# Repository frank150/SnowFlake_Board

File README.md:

# SnowFlake_Board
Circuito impreso navideño en forma de copo de nieve.
# Descripción
Esta PCB es un copo de nieve para decorar tu arbolito navideño el cual encenderá led multicolor de destello lento
# Lista de componentes
Lista de componentes electrónicos usados:
* 6 RGB0807
* 1 Batt HLD-001
* 1 Switch 1825232-1

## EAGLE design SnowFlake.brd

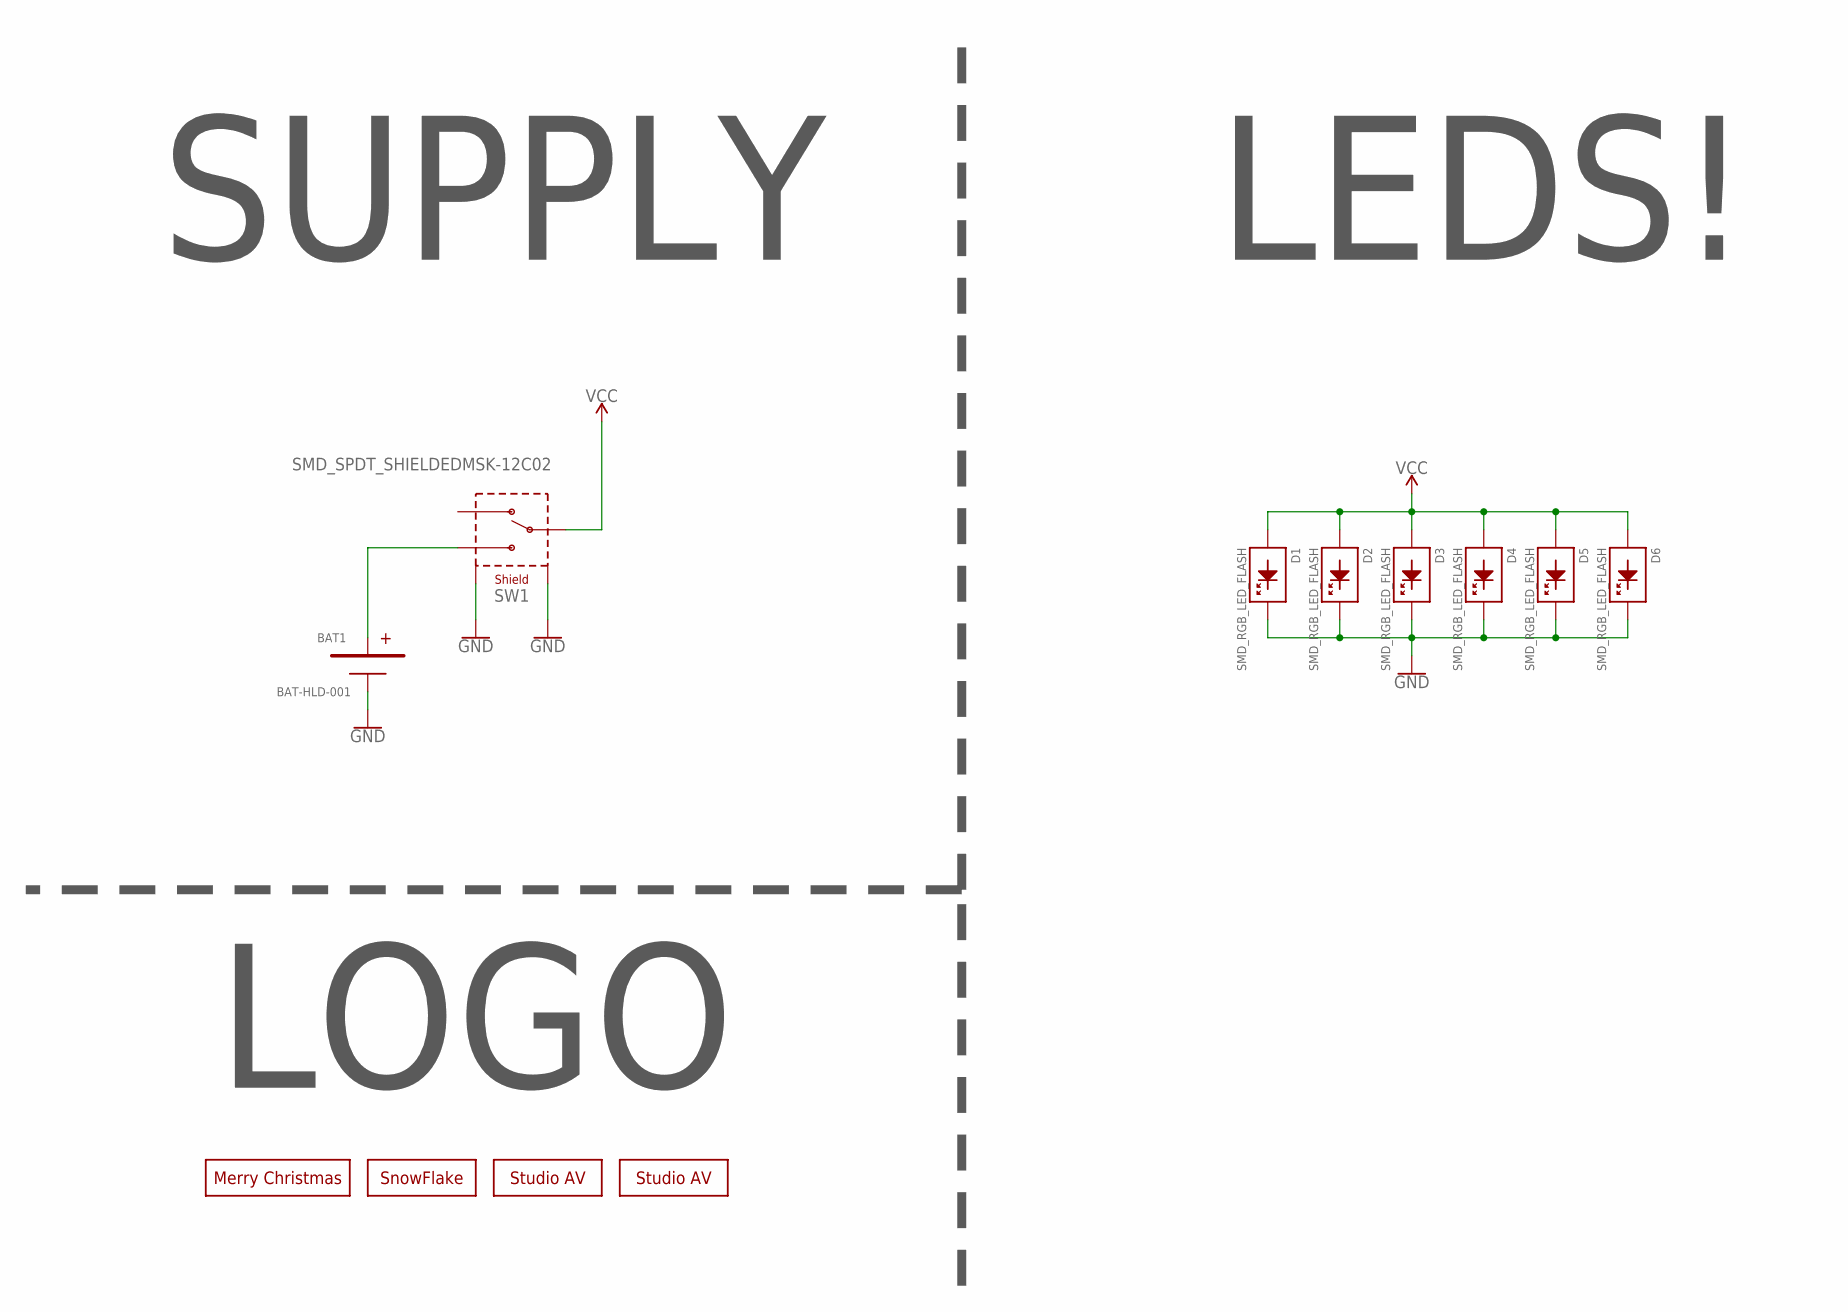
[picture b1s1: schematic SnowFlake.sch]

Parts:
BAT1: BAT-HLD-001; BATHLD001
D1, D2, D3, D4, D5, D6: SMD_RGB_LED_FLASH; SMD_RGB_LED_0807
SW1: SMD_SPDT_SHIELDEDMSK-12C02; MSK-12C02
U$1: MERRY_CHRISTMAS
U$2: STUDIO_AV-QR_CODE; STUDIO_AV_QR
U$3: STUDIO_AV-GENERAL; STUDIO_AV
U$4: SNOWFLAKE

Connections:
GND: BAT1.3 (N), D1.3 (K), D1.4 (K), D2.3 (K), D2.4 (K), D3.3 (K), D3.4 (K), D4.3 (K), D4.4 (K), D5.3 (K), D5.4 (K), D6.3 (K), D6.4 (K), SW1.GND@1 (S1), SW1.GND@2 (S2), SW1.GND@3 (S1), SW1.GND@4 (S2)
unnamed: BAT1.1, BAT1.2, SW1.L2 (NO)
VCC: D1.1 (A), D1.2 (A), D2.1 (A), D2.2 (A), D3.1 (A), D3.2 (A), D4.1 (A), D4.2 (A), D5.1 (A), D5.2 (A), D6.1 (A), D6.2 (A), SW1.COM (C)

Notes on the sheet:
SUPPLY
LEDS!
LOGO

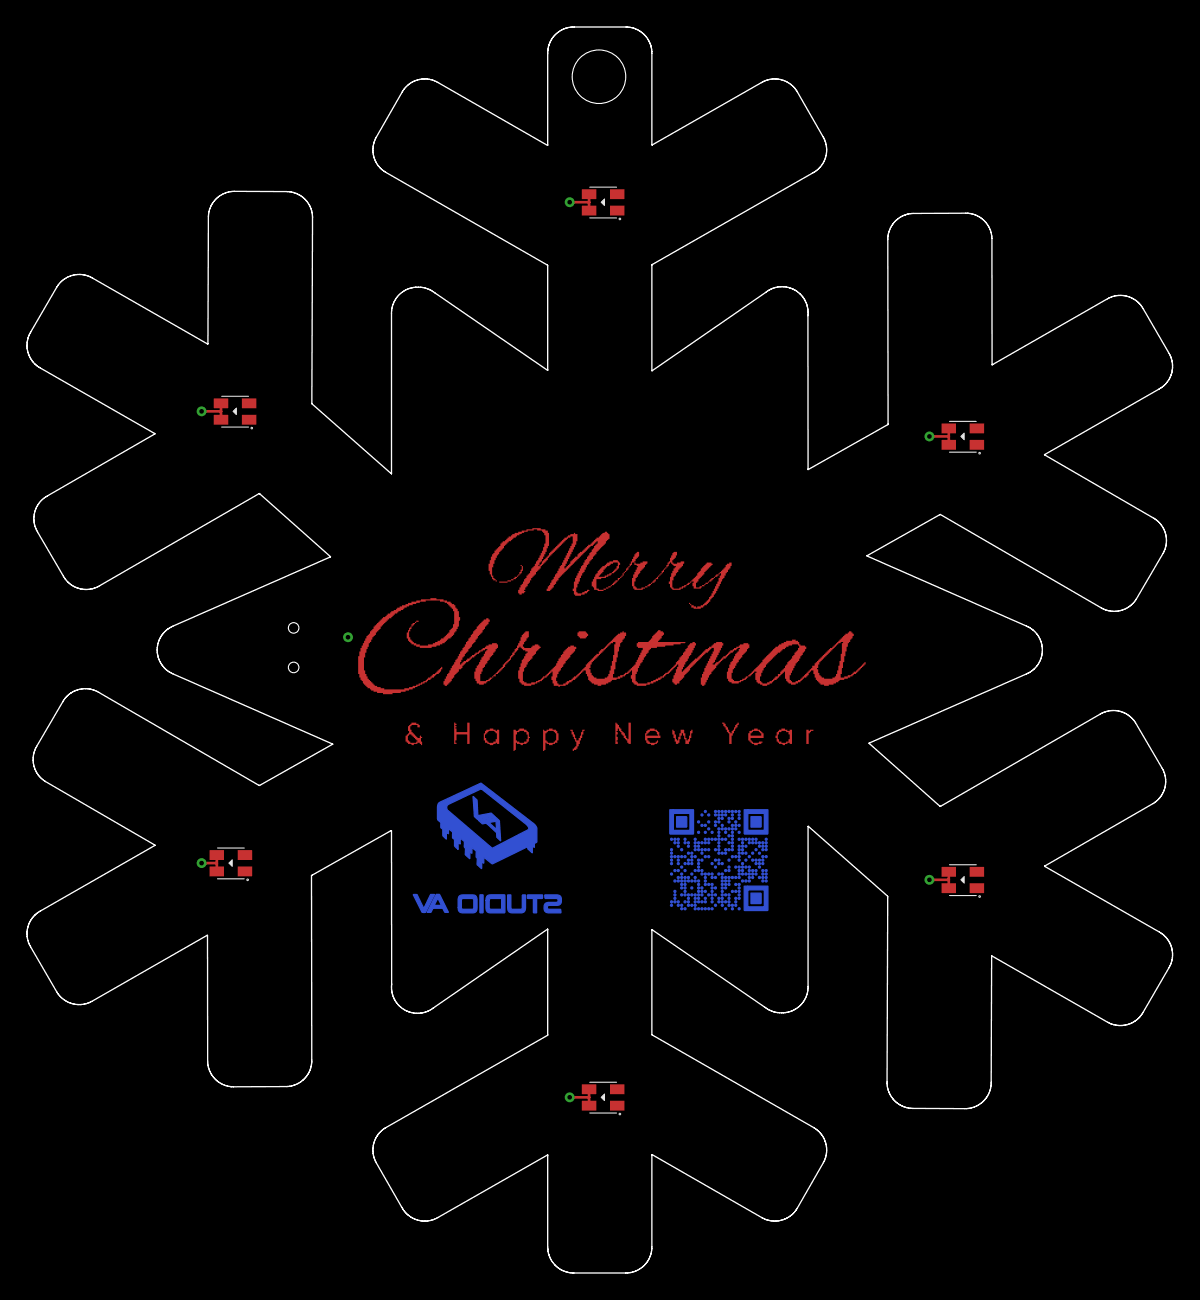
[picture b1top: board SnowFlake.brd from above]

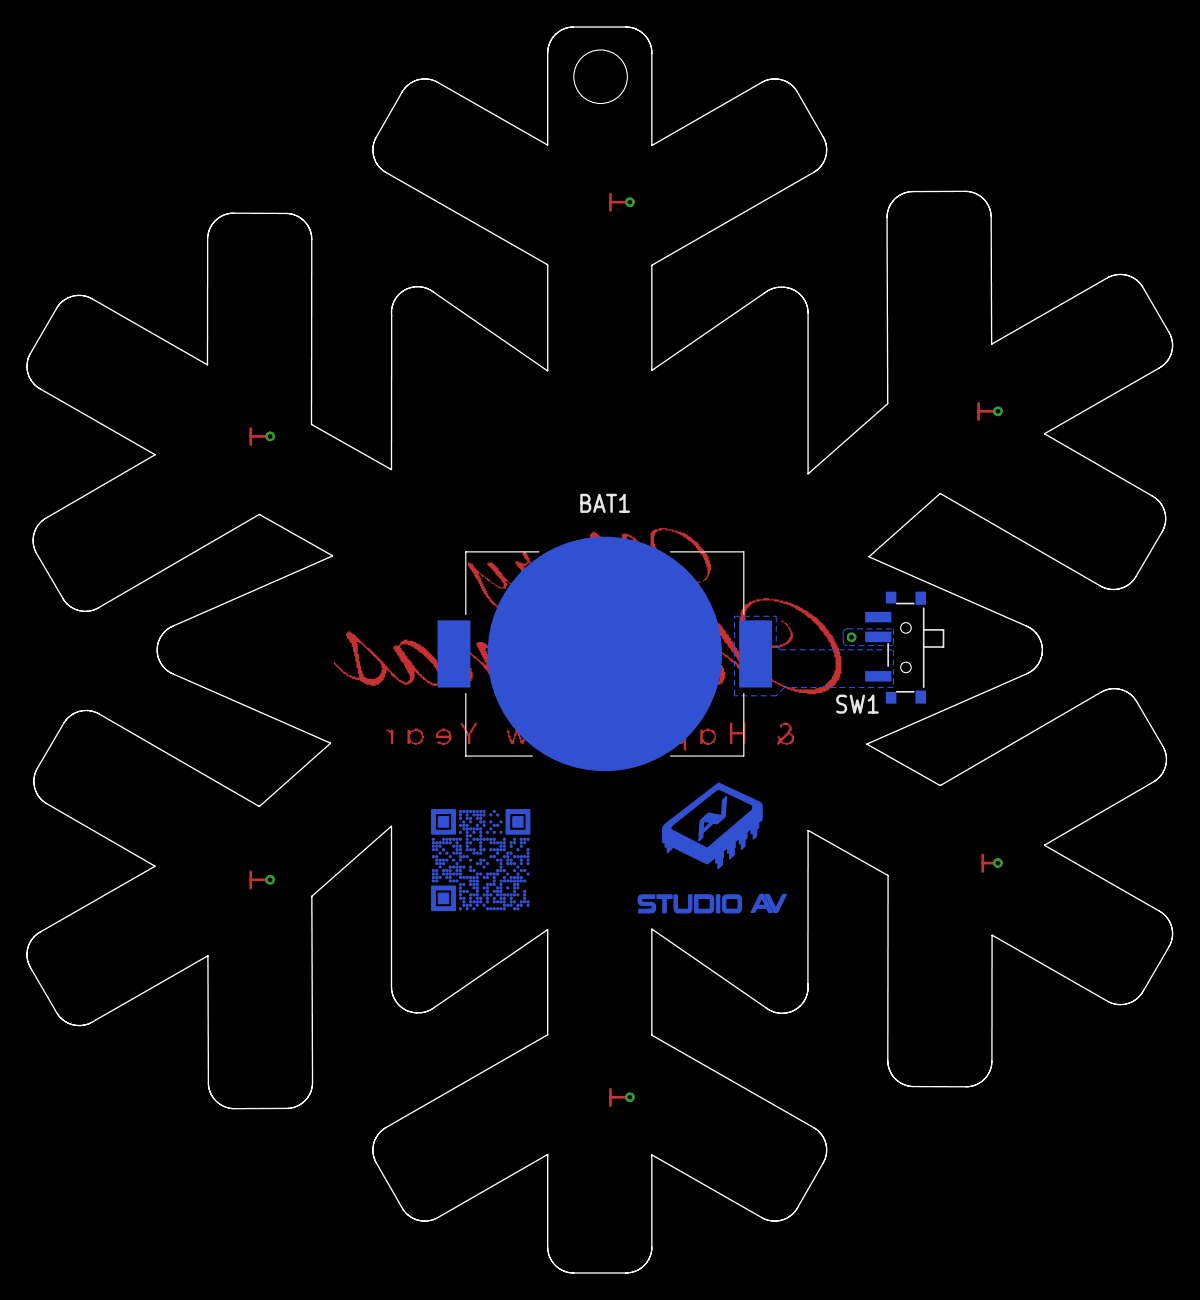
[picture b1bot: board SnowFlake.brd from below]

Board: 2 copper layers, 87.0 x 94.6 mm, 12 parts (4 on the bottom side), 3 nets.
